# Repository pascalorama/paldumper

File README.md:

# paldumper
PCB design for the pal dumper created by Charles MacDonald

all infos are available at http://techno-junk.org/readpal.php

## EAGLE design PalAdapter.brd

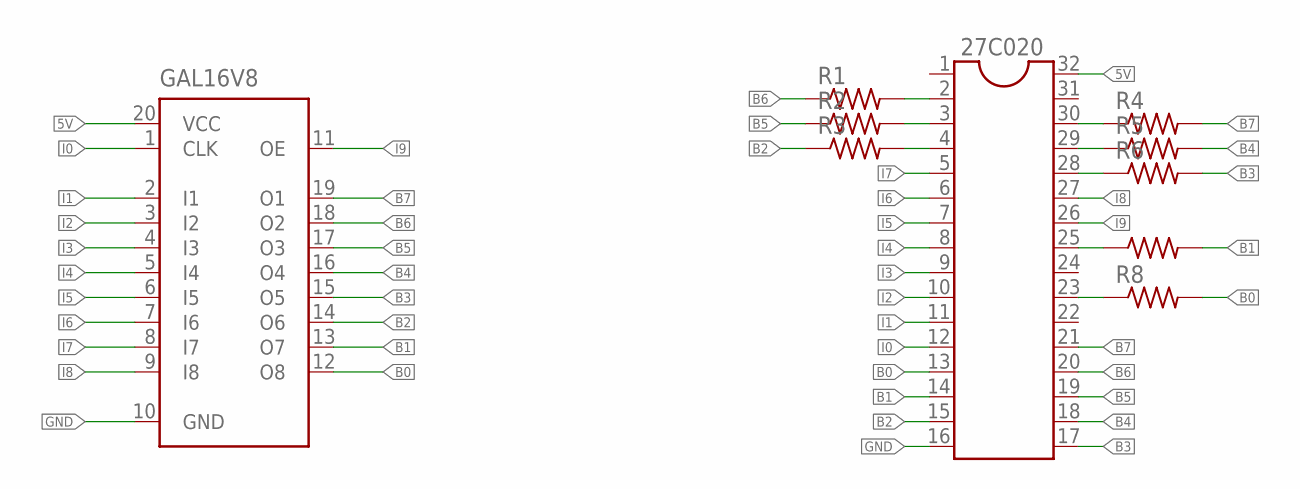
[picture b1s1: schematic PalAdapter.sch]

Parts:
27C020: DIL32
GAL16V8: ATF16V8BP3; DIL20
R1, R2, R3, R4, R5, R6, R7, R8: R-US_0204/7; 0204/7

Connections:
5V: 27C020.32, GAL16V8.20 (VCC)
B0: 27C020.13, GAL16V8.12 (O8), R8.2
B1: 27C020.14, GAL16V8.13 (O7), R7.2
B2: 27C020.15, GAL16V8.14 (O6), R3.1
B3: 27C020.17, GAL16V8.15 (O5), R6.2
B4: 27C020.18, GAL16V8.16 (O4), R5.2
B5: 27C020.19, GAL16V8.17 (O3), R2.1
B6: 27C020.20, GAL16V8.18 (O2), R1.1
B7: 27C020.21, GAL16V8.19 (O1), R4.2
GND: 27C020.16, GAL16V8.10 (GND)
I0: 27C020.12, GAL16V8.1 (CLK)
I1: 27C020.11, GAL16V8.2 (I1)
I2: 27C020.10, GAL16V8.3 (I2)
I3: 27C020.9, GAL16V8.4 (I3)
I4: 27C020.8, GAL16V8.5 (I4)
I5: 27C020.7, GAL16V8.6 (I5)
I6: 27C020.6, GAL16V8.7 (I6)
I7: 27C020.5, GAL16V8.8 (I7)
I8: 27C020.27, GAL16V8.9 (I8)
I9: 27C020.26, GAL16V8.11 (OE)
unnamed: 27C020.2, R1.2
unnamed: 27C020.3, R2.2
unnamed: 27C020.4, R3.2
unnamed: 27C020.30, R4.1
unnamed: 27C020.29, R5.1
unnamed: 27C020.28, R6.1
unnamed: 27C020.25, R7.1
unnamed: 27C020.23, R8.1

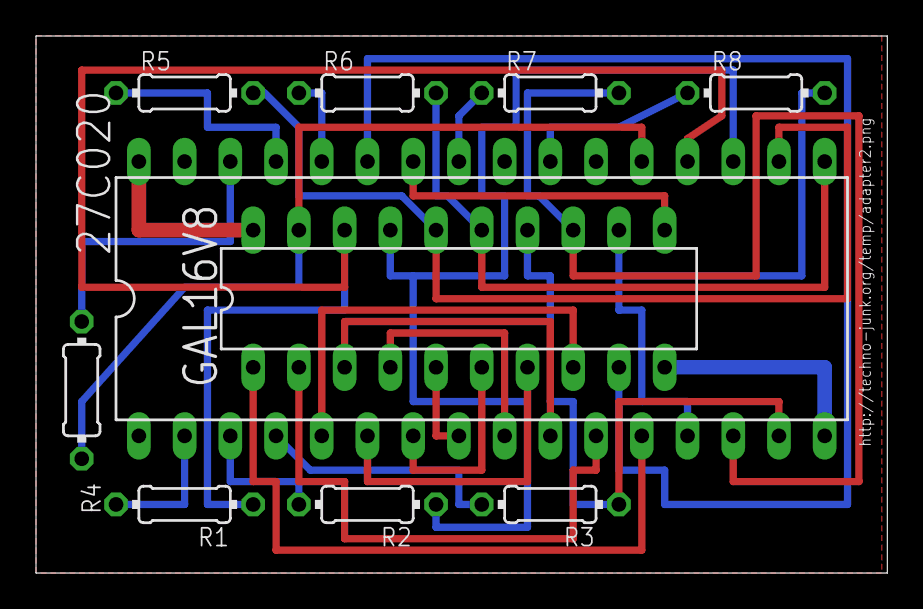
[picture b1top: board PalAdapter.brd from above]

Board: 2 copper layers, 47.3 x 29.8 mm, 10 parts (0 on the bottom side), 28 nets.

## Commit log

2017-06-25 initial release
    initial release. tested working with a Batronix Batego 2
